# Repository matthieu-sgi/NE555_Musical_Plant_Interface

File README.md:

# NE555 Musical Plant Interface 

This repository contains the source files of the PCB made for the project.
The project is built on Kicad V6.

## Goal

This PCB aims to replace the previous heavy system. The previous system was capturing the changes of resistance through the oscillation of a NE555 module.

The frequency was then turned into MIDI, transferred to a MIDI synthetizer, went through a guitar effect pedal and then played on a speaker. This sound is in high resolution and can be used to play music.

The new system is based on a esp32 still capturing the frequency of the NE555. The use of the `mozzi` library allows to play the sound directly on the speaker. The sound is not in high resolution but it is still possible to play music. The sound is amplified using a LM386.

## Components

You can find the non-default components in the `components` folder. This includes the schematic and the footprint.

## PCB

The PCB is made in 2 copper layers. 
The top layer also includes a ground plane that permits to reduce the noise.

The main components of the PCB are :

* ESP32-WROOM-32 (SMT)
* 2x 3.5mm jack (THT)
* Mini DC jack (THT)
* LM386 (THT)
* NE555 (THT)
* Micro-SD slot (SMT)
* LM317 (SMT)

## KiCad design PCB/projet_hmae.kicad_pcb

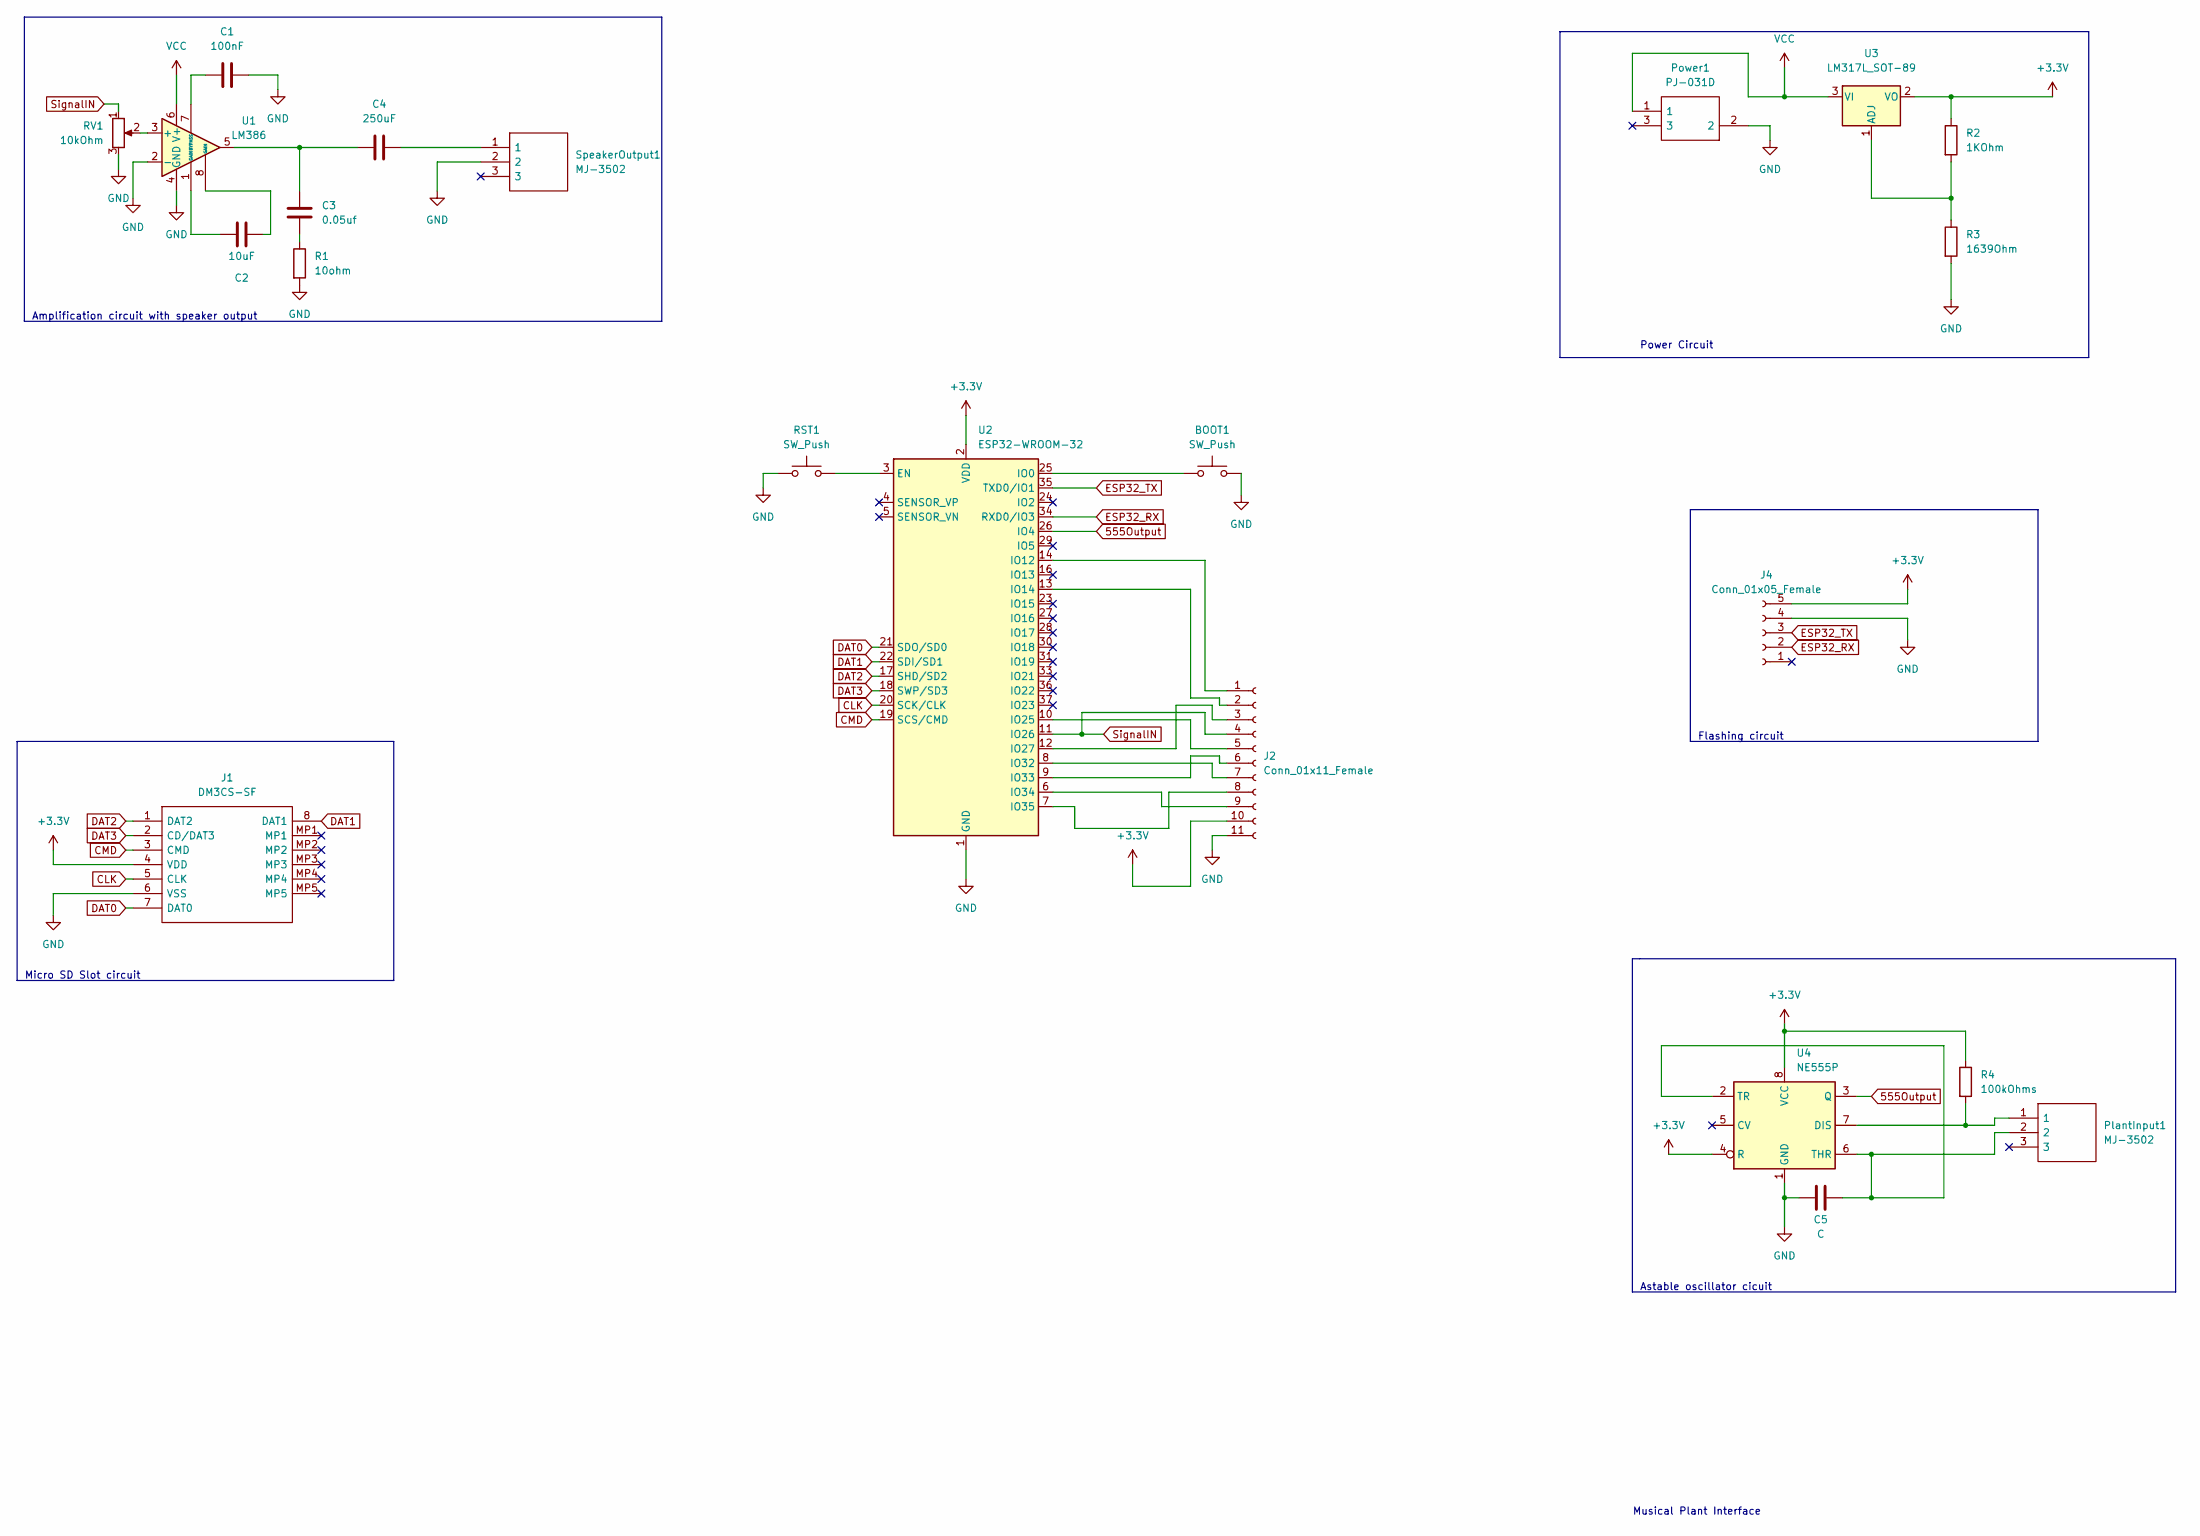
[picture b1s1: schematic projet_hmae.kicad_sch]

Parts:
BOOT1: SW_Push; SW_SPST_EVQP0
C1: 100nF; C_0603_1608Metric_Pad1.08x0.95mm_HandSolder
C2: 10uF; C_0603_1608Metric_Pad1.08x0.95mm_HandSolder
C3: 0.05uf; C_0603_1608Metric_Pad1.08x0.95mm_HandSolder
C4: 250uF; C_0603_1608Metric_Pad1.08x0.95mm_HandSolder
C5: C; C_0603_1608Metric_Pad1.08x0.95mm_HandSolder
J1: DM3CS-SF; DM3CSSF; Mouser Part Number 798-DM3CSSF
J2: Conn_01x11_Female; PinHeader_1x11_P2.54mm_Vertical
J4: Conn_01x05_Female; PinHeader_1x05_P2.54mm_Horizontal
PlantInput1: MJ-3502; MJ3502; Mouser Part Number 490-MJ-3502
Power1: PJ-031D; PJ031D; Mouser Part Number 490-PJ-031D
R1: 10ohm; R_1206_3216Metric_Pad1.30x1.75mm_HandSolder
R2: 1KOhm; R_1206_3216Metric_Pad1.30x1.75mm_HandSolder
R3: 1639Ohm; R_1206_3216Metric_Pad1.30x1.75mm_HandSolder
R4: 100kOhms; R_1206_3216Metric_Pad1.30x1.75mm_HandSolder
RST1: SW_Push; SW_SPST_EVQP0
RV1: 10kOhm; Potentiometer_ACP_CA9-V10_Vertical
SpeakerOutput1: MJ-3502; MJ3502; Mouser Part Number 490-MJ-3502
U1: LM386; DIP794W45P254L959H508Q8
U2: ESP32-WROOM-32
U3: LM317L_SOT-89; SOT-89-3
U4: NE555P; DIP-8_W7.62mm

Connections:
555Output: U2.26 (IO4), U4.3 (Q)
+3V3: J1.4 (VDD), J2.10, J4.5, R2.1, R4.1, U2.2 (VDD), U3.2 (VO), U4.4 (R), U4.8 (VCC)
CLK: J1.5 (CLK), U2.20 (SCK/CLK)
CMD: J1.3 (CMD), U2.19 (SCS/CMD)
DAT0: J1.7 (DAT0), U2.21 (SDO/SD0)
DAT1: J1.8 (DAT1), U2.22 (SDI/SD1)
DAT2: J1.1 (DAT2), U2.17 (SHD/SD2)
DAT3: J1.2 (CD/DAT3), U2.18 (SWP/SD3)
ESP32_RX: J4.2, U2.34 (RXD0/IO3)
ESP32_TX: J4.3, U2.35 (TXD0/IO1)
GND: BOOT1.2, C1.2, C5.1, J1.6 (VSS), J2.11, J4.4, Power1.2, R1.2, R3.2, RST1.1, RV1.3, SpeakerOutput1.2, U1.2 (-), U1.4 (GND), U2.1 (GND), U2.15 (GND), U2.38 (GND), U2.39 (GND), U4.1 (GND)
unnamed: BOOT1.1, U2.25 (IO0)
unnamed: C1.1, U1.7 (BYPASS)
unnamed: C2.1, U1.1 (GAIN)
unnamed: C2.2, U1.8 (GAIN)
unnamed: C3.1, C4.1, U1.5
unnamed: C3.2, R1.1
unnamed: C4.2, SpeakerOutput1.1
unnamed: C5.2, PlantInput1.2, U4.2 (TR), U4.6 (THR)
unnamed: J2.1, U2.14 (IO12)
unnamed: J2.2, U2.13 (IO14)
unnamed: J2.3, U2.12 (IO27)
unnamed: J2.5, U2.10 (IO25)
unnamed: J2.6, U2.9 (IO33)
unnamed: J2.7, U2.8 (IO32)
unnamed: J2.8, U2.7 (IO35)
unnamed: J2.9, U2.6 (IO34)
unnamed: PlantInput1.1, R4.2, U4.7 (DIS)
unnamed: R2.2, R3.1, U3.1 (ADJ)
unnamed: RST1.2, U2.3 (EN)
unnamed: RV1.2, U1.3 (+)
SignalIN: J2.4, RV1.1, U2.11 (IO26)
VCC: Power1.1, U1.6 (V+), U3.3 (VI)

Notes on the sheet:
Musical Plant Interface
Amplification circuit with speaker output
Power Circuit
Astable oscillator cicuit
Micro SD Slot circuit
Flashing circuit

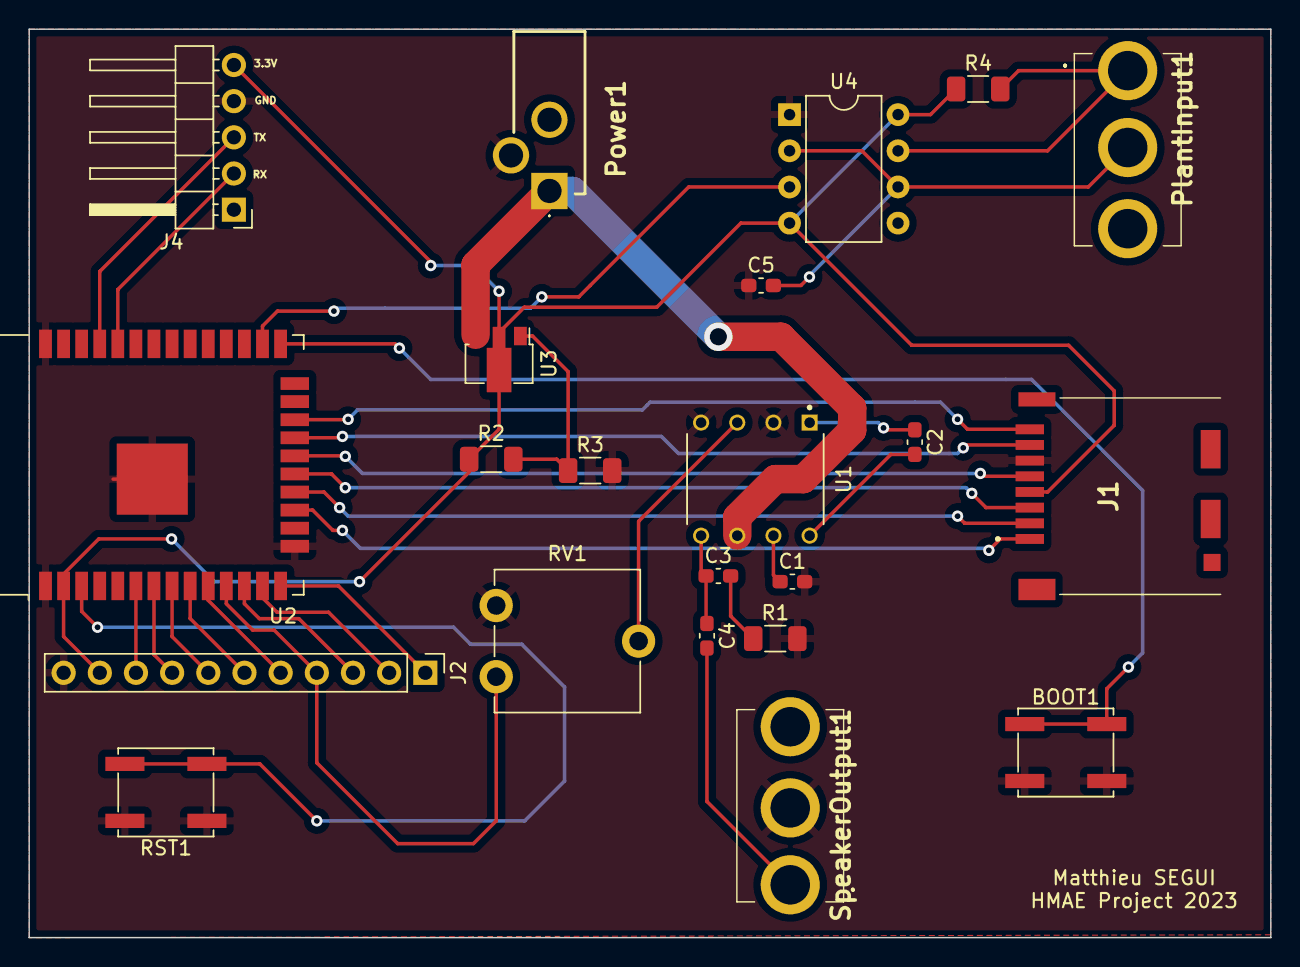
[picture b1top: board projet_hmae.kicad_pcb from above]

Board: 2 copper layers, 87.2 x 63.8 mm, 22 parts (0 on the bottom side), 33 nets.

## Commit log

2023-03-23 First
2023-03-23 Added READMES
2023-03-29 Media
